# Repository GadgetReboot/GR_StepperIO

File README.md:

# GR_StepperIO
Dual Stepper module PCB with Arduino Pro Micro, PCF8574, and various sensor/switch IO's

BOM: working on document to be uploaded here

Video:

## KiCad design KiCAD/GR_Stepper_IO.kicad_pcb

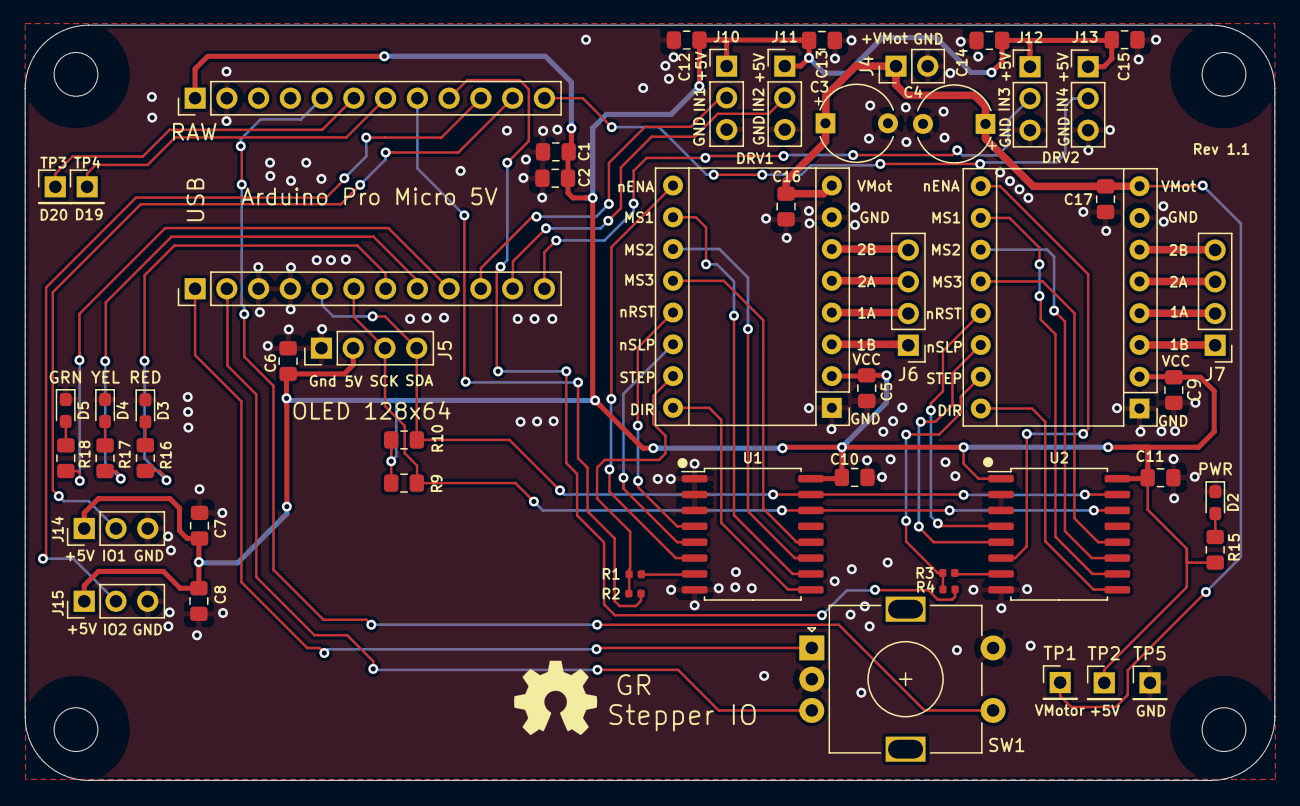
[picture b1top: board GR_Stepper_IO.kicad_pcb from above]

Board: 2 copper layers, 99.9 x 60.4 mm, 53 parts (0 on the bottom side), 51 nets.

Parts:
C1: 4.7uF; C_0805_2012Metric_Pad1.15x1.40mm_HandSolder
C2, C5, C6, C7, C8, C9, C10, C11, C12, C13, C14, C15, C16, C17: 100nF; C_0805_2012Metric_Pad1.15x1.40mm_HandSolder
C3, C4: 47uF 50V; CP_Radial_Tantal_D6.0mm_P5.00mm
D2, D3, D4, D5: LED; LED_0603_1608Metric_Pad1.05x0.95mm_HandSolder
DRV1, DRV2: A4988 Module; Pololu_Breakout-16_15.2x20.3mm
J1, J2: Conn_01x12; PinHeader_1x12_P2.54mm_Vertical
J4: Conn_01x02; PinHeader_1x02_P2.54mm_Vertical
J5, J6, J7: Conn_01x04; PinHeader_1x04_P2.54mm_Vertical
J10, J11, J12, J13, J14, J15: Conn_01x03; PinHeader_1x03_P2.54mm_Vertical
R1, R3: 0r; R_0402_1005Metric
R2, R4: DNI; R_0402_1005Metric
R9, R10: 10K; R_0805_2012Metric_Pad1.15x1.40mm_HandSolder
R15, R16, R17, R18: 1K; R_0805_2012Metric_Pad1.15x1.40mm_HandSolder
SW1: Rotary_Encoder_Switch; RotaryEncoder_Alps_EC11E-Switch_Vertical_H20mm
TP1, TP2, TP3, TP4, TP5: Conn_01x01; PinHeader_1x01_P2.54mm_Vertical
U1, U2: PCF8574; SOIC-16W_7.5x10.3mm_P1.27mm

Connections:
/ENC_A: J1.1, SW1.A
/ENC_B: J1.2, SW1.B
/ENC_SW: J2.5, SW1.S1
/GRN: J1.9, R18.1
/IN1: J1.10, J10.2
/IN2: J1.11, J11.2
/IN3: J1.12, J12.2
/IN4: J2.12, J13.2
/IO1: J2.11, J14.2
/IO2: J2.10, J15.2
/M1_1A: DRV1.4, J6.2
/M1_1B: DRV1.3, J6.1
/M1_2A: DRV1.5, J6.3
/M1_2B: DRV1.6, J6.4
/M1_DIR: DRV1.16, U1.9
/M1_MS1: DRV1.10, U1.10
/M1_MS2: DRV1.11, U1.11
/M1_MS3: DRV1.12, U1.12
/M1_STEPa: R1.2, U1.7
/M1_STEPb: J2.8, R2.2
/M1_STP: DRV1.15, R1.1, R2.1
/M1_nENA: DRV1.9, U1.6
/M1_nRST: DRV1.13, U1.4
/M1_nSLP: DRV1.14, U1.5
/M2_1A: DRV2.4, J7.2
/M2_1B: DRV2.3, J7.1
/M2_2A: DRV2.5, J7.3
/M2_2B: DRV2.6, J7.4
/M2_DIR: DRV2.16, U2.9
/M2_MS1: DRV2.10, U2.10
/M2_MS2: DRV2.11, U2.11
/M2_MS3: DRV2.12, U2.12
/M2_STEPa: R3.2, U2.7
/M2_STEPb: J2.9, R4.2
/M2_STP: DRV2.15, R3.1, R4.1
/M2_nENA: DRV2.9, U2.6
/M2_nRST: DRV2.13, U2.4
/M2_nSLP: DRV2.14, U2.5
/RED: J1.7, R16.1
/SCK: J1.6, J5.3, R9.1, U1.14, U2.14
/SDA: J1.5, J5.4, R10.1, U1.15, U2.15
/SPARE1: J2.6, TP3.1
/SPARE2: J2.7, TP4.1
/YEL: J1.8, R17.1
GNDREF: C1.2, C2.2, C3.2, C4.2, C5.2, C6.2, C7.2, C8.2, C9.2, C10.2, C11.2, C12.2, C13.2, C14.2, C15.2, C16.2, C17.2, D2.1, D3.1, D4.1, D5.1, DRV1.1, DRV1.7, DRV2.1, DRV2.7, J1.3, J1.4, J2.2, J4.2, J5.1, J10.3, J11.3, J12.3, J13.3, J14.3, J15.3, SW1.C, SW1.S2, TP5.1, U1.1, U1.2, U1.3, U1.8, U2.2, U2.3, U2.8
unnamed: D2.2, R15.2
unnamed: D3.2, R16.2
unnamed: D4.2, R17.2
unnamed: D5.2, R18.2
VCC: C1.1, C2.1, C5.1, C6.1, C7.1, C8.1, C9.1, C10.1, C11.1, C12.1, C13.1, C14.1, C15.1, DRV1.2, DRV2.2, J2.1, J5.2, J10.1, J11.1, J12.1, J13.1, J14.1, J15.1, R9.2, R10.2, R15.1, TP2.1, U1.16, U2.1, U2.16
Vdrive: C3.1, C4.1, C16.1, C17.1, DRV1.8, DRV2.8, J4.1, TP1.1
